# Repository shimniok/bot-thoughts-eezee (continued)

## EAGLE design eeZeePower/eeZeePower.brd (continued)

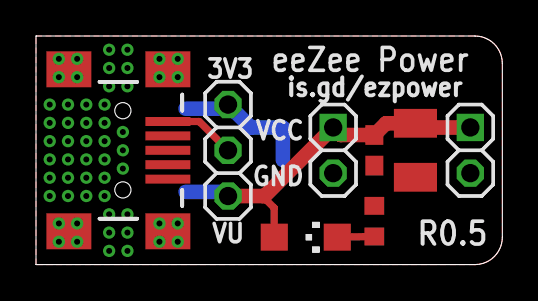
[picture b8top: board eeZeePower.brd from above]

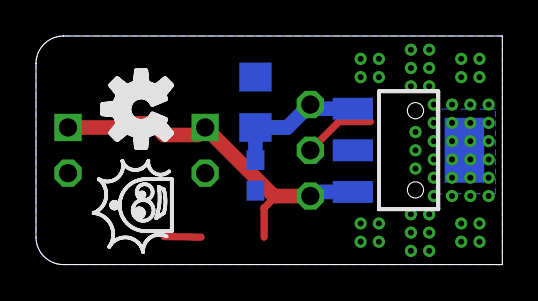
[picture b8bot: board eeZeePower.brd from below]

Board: 2 copper layers, 25.9 x 12.7 mm, 11 parts (3 on the bottom side), 5 nets.

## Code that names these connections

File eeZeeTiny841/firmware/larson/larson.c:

/** ATtiny841 test
 * 
 * Author: Michael Shimniok (www.bot-thoughts.com)
 * Description: Sequentially turns on a single pin on PA0-7 and PB0-2. PB3 is reset, PB0, PB1 are XTAL
 *   but still usable if fuses are set to use internal oscillator. Assumes Tiny is sourcing current
 *   to LED (active high)
 *
 */
#include <avr/io.h>
#include <avr/interrupt.h>
#include <util/delay.h>

#define DELAY 100

int main()
{
	int i;

	DDRA=0xff; // All PORTA as output
	DDRB=0x07; // PB0-2, PB3 is reset, PB0, PB1 are XTAL
	
	PORTA=0;
	PORTB=0;

	while (1) {
		for (i = 0; i < 8; i++) {
			PORTA = (1 << i);
			_delay_ms(DELAY);
		}
		PORTA = 0;
		for (i = 2; i >= 0; i--) {
			PORTB = (1 << i);
			_delay_ms(DELAY);
		}
		for (i = 0; i < 3; i++) {
			PORTB = (1 << i);
			_delay_ms(DELAY);
		}
		PORTB = 0;
		for (i = 7; i >= 0; i--) {
			PORTA = (1 << i);
			_delay_ms(DELAY);
		}
	}

}

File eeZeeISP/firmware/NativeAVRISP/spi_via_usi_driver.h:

#ifndef __SPI_DRIVER_H
#define __SPI_DRIVER_H

// This file has been prepared for Doxygen automatic documentation generation.
/*! \file ********************************************************************
*
* Atmel Corporation
*
* \li File:               spi_via_usi_driver.c
* \li Compiler:           IAR EWAAVR 3.10c
* \li Support mail:       avr@atmel.com
*
* \li Supported devices:  All devices with Universal Serial Interface (USI)
*                         capabilities can be used.
*                         The example is written for ATmega169.
*
* \li AppNote:            AVR319 - Using the USI module for SPI communication.
*
* \li Description:        Example on how to use the USI module for communicating
*                         with SPI compatible devices. The functions and variables
*                         prefixed 'spiX_' can be renamed to be able to use several
*                         spi drivers (using different interfaces) with similar names.
*                         Some basic SPI knowledge is assumed.
*
*                         $Revision: 1.4 $
*                         $Date: Monday, September 13, 2004 12:08:54 UTC $
****************************************************************************/
#include <avr/io.h>
#include <avr/interrupt.h>



/* USI port and pin definitions.
 */
#define USI_OUT_REG		PORTA	//!< USI port output register.
#define USI_IN_REG		PINA	//!< USI port input register.
#define USI_DIR_REG		DDRA	//!< USI port direction register.
#define USI_CLOCK_PIN	PA4		//!< USI clock I/O pin.
#define USI_DATAOUT_PIN	PA5		//!< USI data output pin.
#define USI_DATAIN_PIN	PA6		//!< USI data input pin.
#define USI_SS_PIN		PA7		//!< USI (Software) Slave Select pin.



/*  Speed configuration:
 *  Bits per second = CPUSPEED / PRESCALER / (COMPAREVALUE+1) / 2.
 *  Maximum = CPUSPEED / 64.
 */
#define TC0_PRESCALER_VALUE 256		//!< Must be 1, 8, 64, 256 or 1024.
#define TC0_COMPARE_VALUE   1		//!< Must be 0 to 255. Minimum 31 with prescaler CLK/1.




/*! \brief  Initialize USI as SPI master.
 *
 *  This function sets up all pin directions and module configurations.
 *  Use this function initially or when changing from slave to master mode.
 *  Note that the stored USIDR value is cleared.
 *
 *  \param spi_mode  Required SPI mode, must be 0 or 1.
 *  In external clock mode 0 (USICS0 = 0), DI is sampled at positive edges, and DO is
 *  changed (USI Data Register is shifted by one) at negative edges. In external clock
 *  mode 1 (USICS0 = 1) data is sampled at negative and output is changed at positive
 *  edges. The USI clock modes corresponds to the SPI data mode 0 and 1.
 */
void spiX_initmaster( char spi_mode );



/*! \brief  Initialize USI as SPI slave.
 *
 *  This function sets up all pin directions and module configurations.
 *  Use this function initially or when changing from master to slave mode.
 *  Note that the stored USIDR value is cleared.
 *
 *  \param spi_mode  Required SPI mode, must be 0 or 1.
 */
void spiX_initslave( char spi_mode );



/*! \brief  Put one byte on bus.
 *
 *  Use this function like you would write to the SPDR register in the native SPI module.
 *  Calling this function in master mode starts a transfer, while in slave mode, a
 *  byte will be prepared for the next transfer initiated by the master device.
 *  If a transfer is in progress, this function will set the write collision flag
 *  and return without altering the data registers.
 *
 *  \returns  0 if a write collision occurred, 1 otherwise.
 */
char spiX_put( unsigned char val );



/*! \brief  Get one byte from bus.
 *
 *  This function only returns the previous stored USIDR value.
 *  The transfer complete flag is not checked. Use this function
 *  like you would read from the SPDR register in the native SPI module.
 */
unsigned char spiX_get();



/*! \brief  Wait for transfer to complete.
 *
 *  This function waits until the transfer complete flag is set.
 *  Use this function like you would wait for the native SPI interrupt flag.
 */
void spiX_wait();

#endif

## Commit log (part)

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2013-01-08 Moved caps, mods to routing, added logos, added SCK indicator mark
2013-01-08 Changed 3-pin header to vertical style (displays better in Eagle)
2013-01-08 Initial revision
2013-01-08 Changed view
2013-01-08 Rev 0.1 as ordered
2013-01-29 Enlarged pads for SOT-23 and SOD123F for easier hand assembly. Slight tweaks to traces.
2013-01-29 Fixed jumper labels
2013-01-29 Edited wiki page eeZeeProp through web user interface.
2013-01-30 Created wiki page through web user interface.
2013-01-30 Edited wiki page eeZeePropRev2 through web user interface.
2013-01-30 Removed FTDI header, revised layout to reduce leading edge clearance on breadboard.
2013-01-30 Rev 0.1 as built
2013-01-31 Revised layout to reduce leading edge and side edge clearances for better breadboarding.
2013-02-04 Minor layout tweaks
2013-02-04 Layout tweaks to fix power pin alignment.
2013-02-12 Revised board layout removing leading edge, using 6x3mm switch and making board narrower. Revised 8-pin tiny pad thickness minimum. Moved reset resistor for easier assembly. Revised and relocated log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
2013-02-12 Rev 0.2 as-ordered
2013-02-12 Revision 0.2 as ordered
2013-02-21 Edited wiki page eeZeeBigTiny through web user interface.
2013-02-22 Rev 0.2 - initial commit
2013-02-22 Corrected HSYNC / VSYNC connections
2013-02-26 Edited wiki page eeZeePower through web user interface.
2013-02-26 Revised board layout to match the new Tiny style, swapping in new reset button
2013-02-28 Added top and bottom board pdfs.
2013-02-28 Updated pdfs to rev 0.3
2013-06-14 Fixes to PropVGA, microSD,
2013-06-14 Renamed to remove space
2013-08-06 Version 0.4, changes some footprints for easier rework, some mods to routing, mitered corners, some other stuff I'm forgetting.
2013-08-06 Rev 0.3 converted to standard 1206 LED, centered components, mitered corners, moved some components around, removed component names.
2013-08-06 Added a folder to the repository
2013-08-06 oops
2013-08-06 Revision 0.3 as ordered
2013-08-06 Rev 0.4 as ordered
2013-08-06 Rev 0.2, mitered corners, changed silk on tantalum to indicate polarity, few minor rearrangements.
2013-08-06 Adding gerbers
2013-08-06 Rev 0.2 as ordered, mitered corners, changed silk on tantalum to indicate polarity, few minor rearrangements.
2013-08-06 Rev 0.2 as ordered, mitered corners, flipped tantalum and added polarity silk screen, changed location of caps/crystals for easier assembly, shrunk board size.
2013-08-06 Rev 0.2 as ordered
2013-08-06 Rev 0.2, shrunk board, mitered corners, added polarity silk to tantalum.
2013-08-06 Rev 0.3 as ordered
2013-10-10 Edited wiki page eeZeeMedTiny through web user interface.
2013-10-11 Edited wiki page eeZeeMicroSD through web user interface.
2013-10-21 Edited wiki page eeZeeTiny through web user interface.
2013-10-25 Renamed microSD files, moved to electronics subfolder
2013-10-25 Added Arduino example code / test
2013-11-10 Moving electronics files into subdir so i can also have example software
2013-11-10 Adding example/test code
2013-11-10 Created electronics and firmware directories so I could host example code.
2013-11-10 Adding firmware examples
2013-11-10 Updated comments
2013-11-11 Adding firmware examples into subdirectory. Moving electronics cad into electronics directory.
2013-11-12 Created new project, eeZee Switch with cap and resistor
2013-11-12 Rev 0.1
2013-11-12 Initial version of breadboard WS2812B
2013-11-22 New product, a DC Jack version of eeZee Power
2013-11-22 R0.1 as ordered
2013-11-25 Moved electronics into separate folder, created firmware example
2013-11-25 Edited wiki page eeZeeRGB through web user interface.
2013-11-25 Edited wiki page eeZeeSwitch through web user interface.
2013-11-25 Edited wiki page PropVGA through web user interface.
2013-11-25 Edited wiki page eeZeeCrystal through web user interface.
2013-11-25 Deleted wiki page PageName through web user interface.
2013-11-25 Revised RGB firmware to maintain approximately constant power
2013-11-25 Removed definitions file, converted to my own ino code, updated license and comments/documentation
2013-12-01 Initial revision of breadboard LED breakout
2013-12-10 Rev 0.3 SMT version of eeZeeVGA as ordered
2013-12-11 Added regulator bypass option for 3.3V FTDI. Increased diode pad sizes.
2014-01-22 Initial draft revision 0.1
2014-01-22 Fixing accidentally flipped schematic. D'oye!
2014-02-04 Fixed silkscreen conflicts. Enlarged DTR/GND labels. Moved other silk labels to different layer, disabled bottom name silk gen.
2014-02-07 Revised to use standard 1206 10uF part, moved bot thoughts silk.
2014-02-07 Added debounce solder jumper so switch can be used as reset. Moved components and silkscreen around to accommodate.
2014-02-19 Replaced regulator with a lower cost one. Rearranged layout. Regulator on top (heat), capacitors on the bottom. Labeling rearranged.
2014-02-20 Edited wiki page eeZeePowerJack through web user interface.
2014-03-01 Example code for ATtiny841
2014-03-01 Minor mods to board/schematic. avrdude config from AVRfreaks forum.
2014-03-01 Renamed avrdude config
2014-03-01 Revised to use non-reset, non-xtal pins.
2014-03-01 Revised hierarchy with electronics subdir
2014-03-18 Subdirectory for multiple firmware examples
2014-03-18 Added larson scanner
2014-03-18 Initial version, larson scanner type demo
2014-03-18 Fixed char / addition / subtraction bug, converted to larson type scanning, back and forth.
2014-03-18 Added hex files for easier testing
2014-03-18 Edited wiki page eeZeeTiny841 through web user interface.
2014-03-29 Created ATtiny13 serial demo, created subdir for blinky light demo
2014-03-31 Converted project to AVR Studio 4, sick of trying to learn gcc assembly when examples are so scarce :)
2014-04-15 Revised pads for IC, revised 10uF filtering cap footprint to 1206.
2014-04-15 Put testing in a loop for convenience.
2014-04-15 Rev 0.3 as ordered.
2014-04-15 Removed extraneous silkscreen
2014-04-15 Oops, minor silkscreen fix. As ordered, R0.3
2014-04-15 Dang.
2014-04-15 As ordered R0.3
2014-04-15 Revised diode placement, silk, pin 1 dot on propeller.
2014-04-15 R0.5a as ordered
2014-04-24 Revised circuit for easier optional debounce, revised silk for better usability.
2014-04-24 eeZee Switch R0.2 as ordered
2014-04-24 Final fixes to board
2014-04-24 R0.2 as ordered
2014-04-24 Renaming to rev #
2014-04-24 I think this is R0.1 as ordered...
2014-04-24 Updated layout, silk, added URL
2014-04-24 Accidentally copied entire tree. Fixed now.
2014-05-12 Fixed include for missing (unnecessary) header
2014-05-15 Converted to standard 1206 10uF, placed input bypass caps on bottom. Rearranged silk, centered pin headers.
2014-05-15 Revised silk, placed input filter caps on bottom, switch 10uF to standard 1206 package, centered pin headers.
2014-07-24 Edited wiki page eeZeeVGA through web user interface.
2014-09-15 Edited wiki page TinyArduino through web user interface.
2014-09-30 Added light_WS2812 library/examples for AVR.
2014-09-30 Minor mods to Arduino firmware. Updated README with info about new AVR examples with light_WS2812 library.
2014-09-30 Added gerbers for main board and test jig. Added test jig sch and brd.
2014-09-30 Added project documentation box thingy.
2014-09-30 Initial version as ordered. Plus some additional goodies recently added since original design.
2014-09-30 Added new example to cycle through colors smoothly, similar to my Arduino demo.
2014-10-13 Tagging initial version of eeZee crystal
2014-10-13 Resized board narrower and aligned to inches. Added silk for multiple frequencies. Mitred corners. Changed silk print sizes.
2014-10-13 Version 0.2 as ordered
2014-10-17 Increaed spacing to 8/10mil for most objects, reduced distance to 10mil.
2014-10-17 Updated DRC with 10mil/8mil spacing, 10mil distances.
2014-10-17 Changed spacing to 10mil/8mil, relocated too-close traces, relocated via
2014-10-17 Changed spaces to 10mil/8mil, relocated trace
2014-10-17 Changed to 8mil spacing, revised all PTH pins to octagon, relocated traces, vias for clearance. Resized traces with clearance problems.
2014-10-17 Converted to 10mil/8mil spacing, changed PTHs to octagon.
2014-10-17 Changed to 10mil/8mil spacing, improved thermal design, connected heatsink to VOUT.
2014-10-17 Updated version #
2014-10-17 Switched to TC1262 regulator, improved thermal design, moved jumper and LED around.
2014-11-08 Removed some test files, added PinTester back
2014-11-15 Revision 0.2 as built
2014-11-15 Modifying tags dir structure.
2014-11-15 Changing directory structure
2014-11-15 Removing bogus tag
2014-11-15 Modified schematic for easier reading, added letter box. Added 20MHz option to board.
2014-11-15 replacing pdfs with pngs
2014-11-15 Adding gerbers and zip for R0.2B
2014-11-26 Added avrdude.conf content for ATtiny841, added README explaining how to set up.Z
2014-11-26 Modified readme to point to web-based help.
2014-12-01 Revision 0.1 as ordered
2014-12-01 Minor updates, added gerbers, zip
2014-12-02 Modified prinout lines. Removed sd.end() because it (no longer?) exists.
2014-12-03 Change to initialize once after reset, repeats tests every 5 secs, shows pass/fail for each.
2015-01-02 Final version of silk
2015-01-02 Rev 0.1 as ordered/built
2015-01-02 Fixed silk pin 1 on LM386, updated version #
2015-04-09 Migrating wiki contents from Google Code
2015-04-24 Revised microSD test for use with new test jig
2015-04-24 Updated file header/comments, author, documentation.
2015-04-24 added gitignore
2015-04-24 updated gerbers for latest production run
2015-04-24 Changed delay
2015-04-24 removed eagle.epf
2015-04-24 Added delay in hopes of AVR Dragon having time to reset after install, fixed minor typos
2015-04-24 minor reformat. fixed loop variables. changed delay
2015-04-24 removed hex file
2015-04-24 Initial version
2015-04-24 initial version of eeZeeISP
2015-04-24 removed eclipse project files
2015-04-24 consolidated eeZeeProp test/firmware/examples
2015-04-24 renamed eeZeeProp directory
2015-04-24 modified gitignore
2015-04-30 changed file permissions
2015-05-01 added Makefile to larson scanner code
2015-05-01 Added 0.1uF decoupling cap for LM386 supply
2015-05-01 Replaced offboard pot with pin header for clarity
2015-05-01 Revised pinout with single ground in attempt to remove ground loop. Revised schematic to use individual pin headers
2015-05-01 Separated gain pin header into individual pins
2015-05-01 Separated variable resistor header into individual pins
2015-05-01 Aesthetic mod
2015-05-01 Added another ground pin, rearrange layout
2015-05-01 Narrowed by 0.1", complete redo of layout, text, accommodated larger 8mm output cap, fitted decoupling 0.1uF, located all gnd near to avoid loop, removed top ground pour
2015-05-01 moved label
2015-05-01 Added title, OSHW logo on both sheets, relabeled gnd, audio in gnd pin header, added gain label, added cc
2015-05-03 Created silk and gerbers
2015-05-04 Updated README to include links to projects.
2015-05-04 Moved LED, RGB, Pot to separate repos
2015-05-04 moved eeZeeAmp to separate repo
2015-05-04 moved eeZee_tiny and eeZee_med_tiny to separate repos
2015-05-04 Modified README.md with links to new separate repos
2015-05-04 moved eeZee Crystal to separate repo
2015-05-04 Moved eeZee Big Tiny to separate repo
2015-05-05 Moved eeZee Switch to separate repository
2015-05-05 Moved eeZeePower, eeZeePowerJack to separate repos
2015-05-05 Moved microSD to separate repo
2015-05-05 Moved eeZeeProp to separate repo
2015-05-05 Removed retired PropVGA directory
2015-05-05 moved eeZeeTiny841 to separate repo
2015-05-06 Moved eeZeeVGA to separate repo
